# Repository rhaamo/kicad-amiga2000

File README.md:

# Amiga 2000 KiCAD Schematics and PCB

# Revision

Current schematics are based on 6.0 plus known 6.2 fixes.

Deviations from the original 6.2:
- The snapped resistor net around the 68k have been removed from schematics.
- The two res net soldered to U603 and U604 have a dedicated footprint on PCB
- The bridge C1/R1 also has footprint, same for R2 from U800
- The PST reset have dedicated footprint, diode have been removed
- There is an aditionnal header, J3, with OVR and INT2 breakout for accelerator cards, easier than clipping on chips
- Jumpers should have a default working configuration labelled on the PCB plus various notes
- The keyboard connector footprint have been modified to handle either the original one, or a standard MIDI one
- The battery terminals are just a two pins header, just plug some wires and use any battery you want aside or glued or whatever

# TODO

- Check if there is no useless local labels that could have generated spurious nets connected in the PCB

# Notes

The capacitors on the left of the POWER Connector are somewhat troubling if you don't have a lot of experience.

So the five caps should be placed like this (IGNORE the + footprint on the PCB):

- C400, GND pin on left
- C406, GND pin on left
- C408, GND pin on right
- C410, GND pin on left
- C412, GND pin on right

If using an A500-Flash from Retro 7-bit, U540 and U203 can't be socketted or they will be too high.

# Building

The file `amiga2000.csv` contains a full Mouser BOM, around ~150€.

Memory and RTC chip should be got from eBay, same for the PST reset thingy (U1).

The ISA (8bit and 16bit connectors) fits perfectly a full-length connector got from like an old PC motherboard.

The the table at the bottom of this README for a list of DigiKey and Mouser P/N for ZORRO, CoPro, Video and ISA slots.

Other chips (paula, denise, CIA, etc.) are got from a donor motherboard.

If building it for real: first test the PCB for short between GND and the various power lines (+5V, -5V, +12V, +5V_USER, etc.), the zorro should have all.

Then solder all the electrolytics caps, connect power, re-test all the lines.

Solder everything else, don't populate ICs yet, re-power and re-test.

Then you can add ICs and run DiagROM and then enjoy.

DO NOT POPULATE: J1, J2, C902, C917, R901, FB904, FB906, RP904, RP906, RP905, C230, C240, they are unpopulated on factory 6.2 rev, so, let them as-is.

# Testing

My first prototype have been tested with DiagROM v1.1.

Working: mouse, zorro listing of detected cards, composite video out, video out, serial (out at least), one audio ch (the other one should work too), keyboard.
Booting a workbench from the accelerator CF sorta work until noise issue or something make any disk I/O hang and crash.

Left to test: floppy, parallel port, if the RTC works properly.

The DiagROM detects 1024kB of chipmem, the extended test goes all the way up to 1023kB and then throw an error, I'm not sure if it's a DiagROM issue or just expected.

# Libraries

Uses libraries from https://dev.sigpipe.me/dashieelectronics/kicad_libraries

# Various tools

## extract_labels.py
NOTE: Broken since format change with KiCAD 7.0

Use this script to quickly extract all Global Labels from wanted sheets.

```
./extract_labels.py agnus.kicad_sch amiga2000.kicad_sch chipram.kicad_sch coprocessor\ slot.kicad_sch denise.kicad_sch expansion\ logic.kicad_sch parallel.kicad_sch paula.kicad_sch pc\ slots.kicad_sch power.kicad_sch processor.kicad_sch serial.kicad_sch zorro.kicad_sch
```

# License

CC0

# Sources

My own dying 6.2 A2000 board.

This pre-6.2 schematics, best scan quality available...:
- http://amiga.serveftp.net/Schematics/A2000_schematics/A2000_rev6_schematics_scanned.pdf

A big thanks for Floppie209 for his 1:1 board replica:
- https://github.com/Floppie209/Amiga2000-remake/

Whithout Floppie work I wouldn't have had enough motivation to sacrifice a sorta working board for measurements.

Documented 6.2 fixes: https://wiki.sigpipe.me/amiga:a2000:rev6.2fixes

# Random parts numbers

| for | Digikey PN | Mouser PN | Manufacturer PN | EOL |
|-----|------------|-----------|-----------------|-----|
| Zorro (100pins) | A121376-ND | 571-5645235-3 | 5645235-3 | no |
| CoPro (86pins) | A144213-ND | 571-1-5530843-0 | 1-5530843-0 | no |
| Video Slots and ISA16bit (36p) | A31716-ND |  571-5530843-3 | 5530843-3 | no |
| ISA 8bit (62) | A121053-ND |  571-7-5530843-0  | 7-5530843-0 | no |
| Full lenght ISA slots | A101941-ND |  571-5176139-2  | 5176139-2 | no |
| Power connector, 14 pins |   | 538-26-60-4140 | 26-60-4140 | no |

# Pictures

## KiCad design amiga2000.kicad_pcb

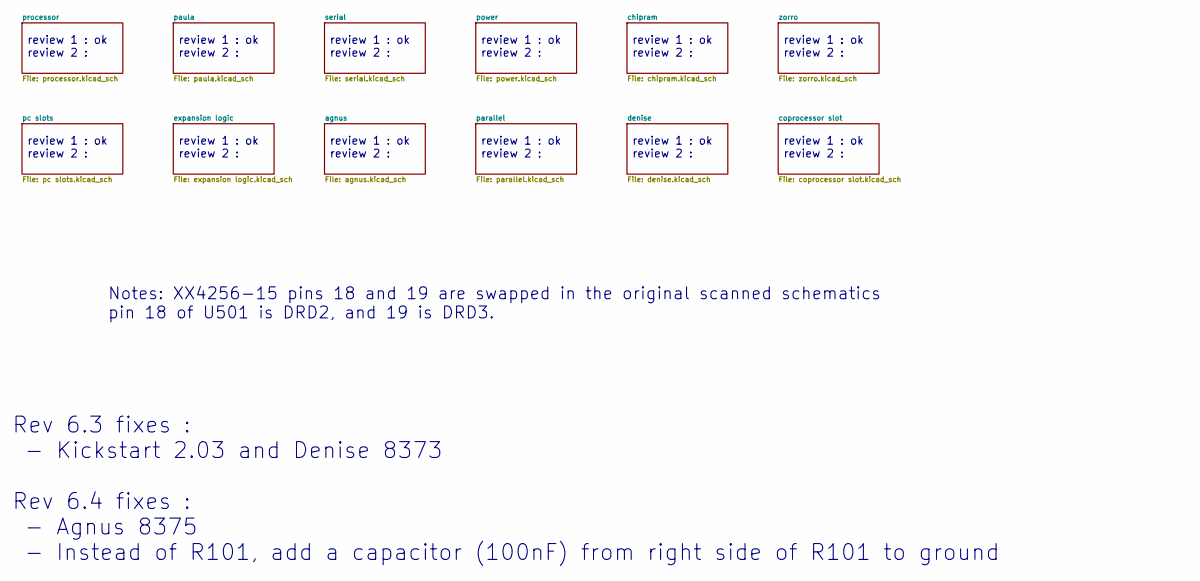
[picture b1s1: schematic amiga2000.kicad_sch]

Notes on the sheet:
review 1 : ok review 2 :
Notes: XX4256-15 pins 18 and 19 are swapped in the original scanned schematics pin 18 of U501 is DRD2, and 19 is DRD3.
Rev 6.3 fixes : - Kickstart 2.03 and Denise 8373 Rev 6.4 fixes : - Agnus 8375 - Instead of R101, add a capacitor (100nF) from right side of R101 to ground

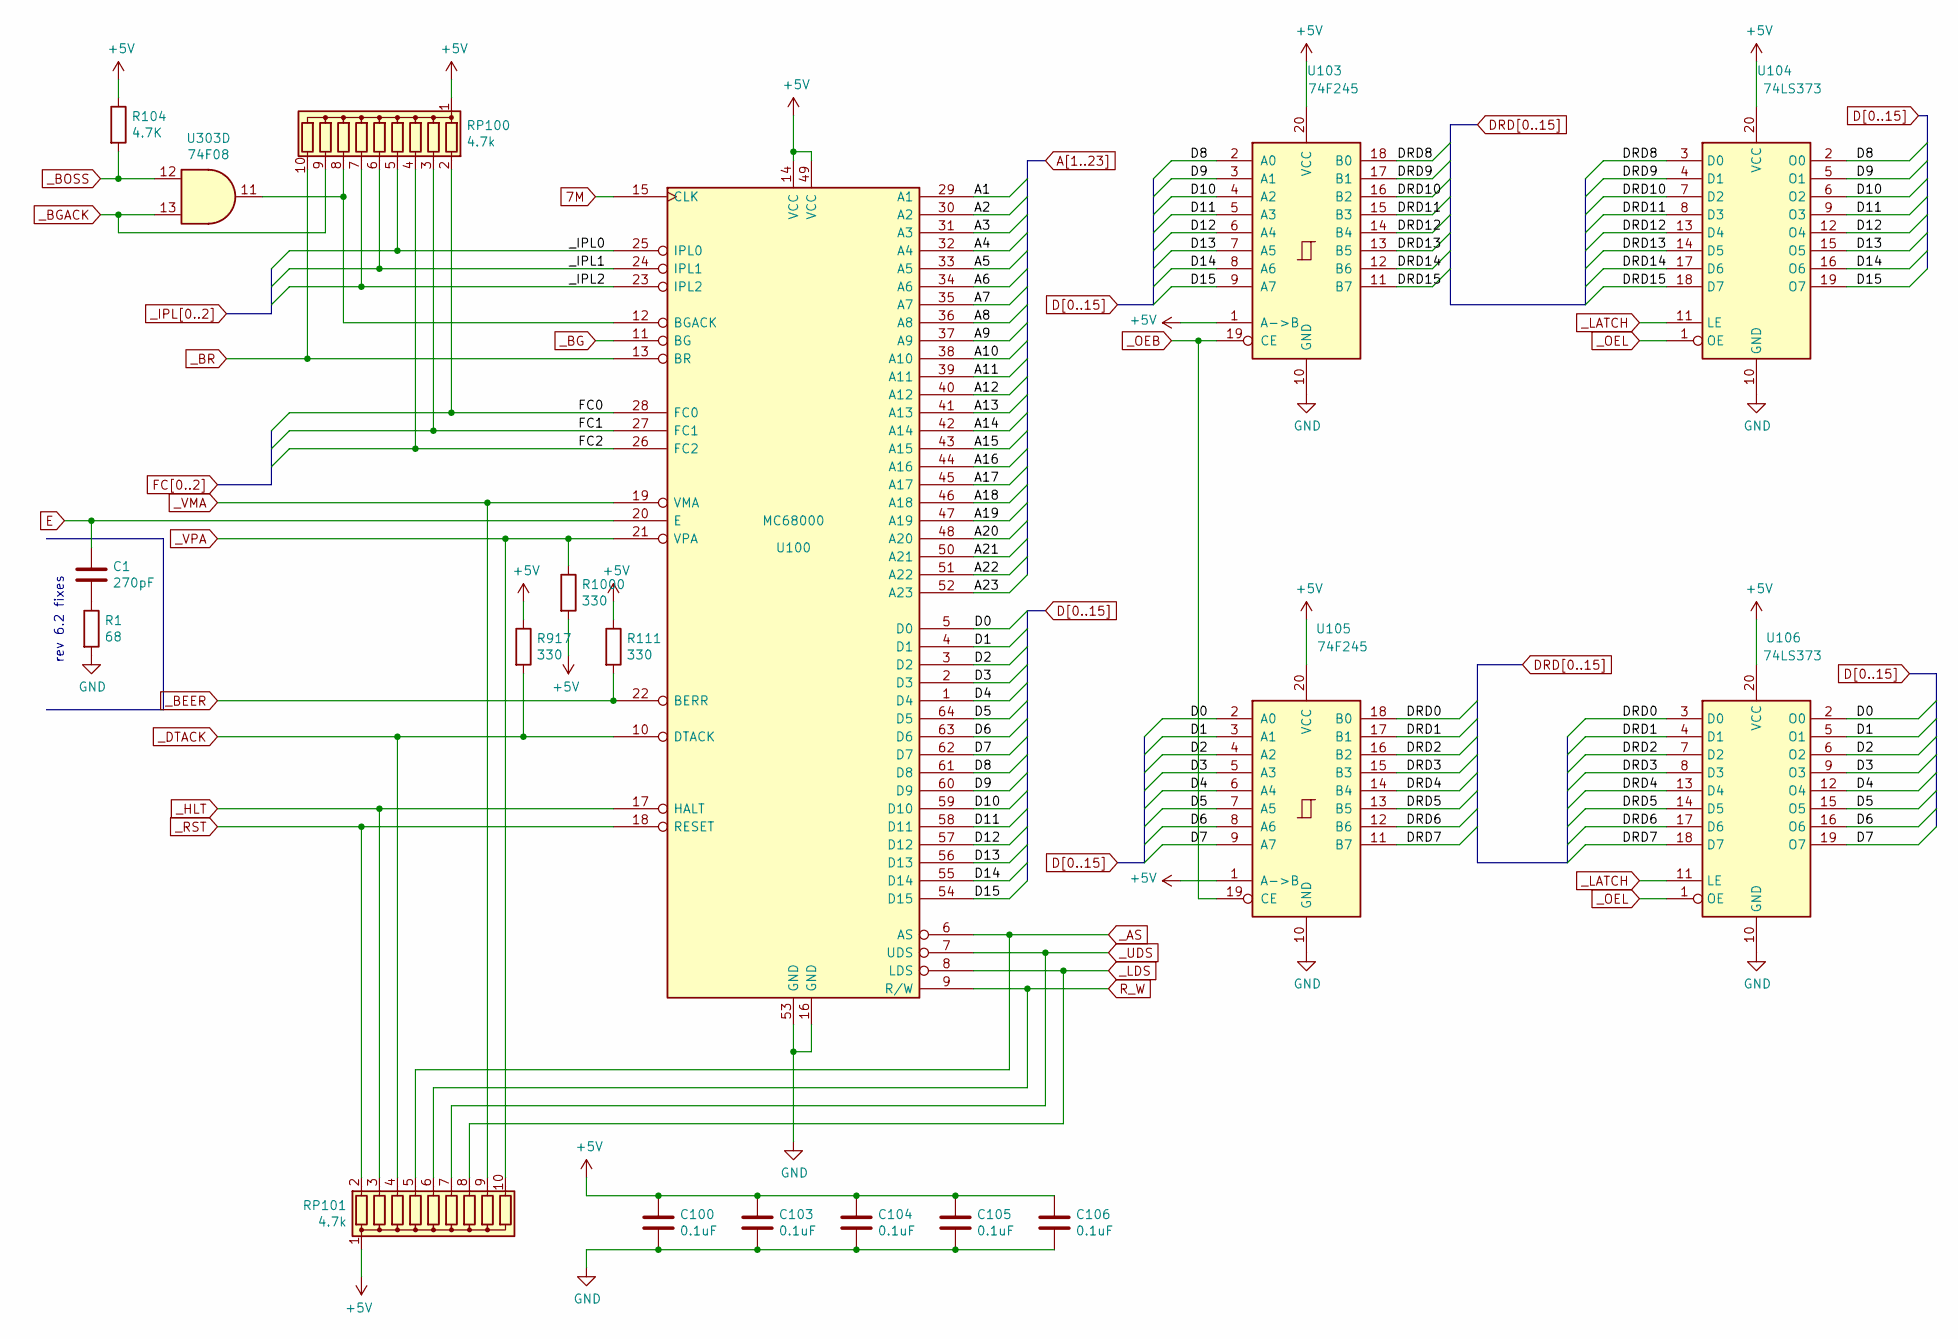
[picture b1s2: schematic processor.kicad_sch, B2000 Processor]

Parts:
C1: 270pF; C_Rect_L11.5mm_W2.6mm_P10.00mm_MKT
C100, C103, C104, C105, C106: 0.1uF; C_Rect_L11.5mm_W2.6mm_P10.00mm_MKT
R1: 68; R_Axial_DIN0207_L6.3mm_D2.5mm_P10.16mm_Horizontal
R104: 4.7K; R_Axial_DIN0207_L6.3mm_D2.5mm_P10.16mm_Horizontal
R111, R917, R1000: 330; R_Axial_DIN0207_L6.3mm_D2.5mm_P10.16mm_Horizontal
RP100, RP101: 4.7k; R_Array_SIP10
U100: MC68000; DIP-64_W22.86mm_Socket
U103, U105: 74F245; DIP-20_W7.62mm_Socket
U104, U106: 74LS373; DIP-20_W7.62mm_Socket
U303: 74F08; DIP-14_W7.62mm_Socket

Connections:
7M: U100.15 (CLK); also elsewhere on the board
A1: U100.29 (A1); also elsewhere on the board
A2: U100.30 (A2); also elsewhere on the board
A3: U100.31 (A3); also elsewhere on the board
A4: U100.32 (A4); also elsewhere on the board
A5: U100.33 (A5); also elsewhere on the board
A6: U100.34 (A6); also elsewhere on the board
A7: U100.35 (A7); also elsewhere on the board
A8: U100.36 (A8); also elsewhere on the board
A9: U100.37 (A9); also elsewhere on the board
A10: U100.38 (A10); also elsewhere on the board
A11: U100.39 (A11); also elsewhere on the board
A12: U100.40 (A12); also elsewhere on the board
A13: U100.41 (A13); also elsewhere on the board
A14: U100.42 (A14); also elsewhere on the board
A15: U100.43 (A15); also elsewhere on the board
A16: U100.44 (A16); also elsewhere on the board
A17: U100.45 (A17); also elsewhere on the board
A18: U100.46 (A18); also elsewhere on the board
A19: U100.47 (A19); also elsewhere on the board
A20: U100.48 (A20); also elsewhere on the board
A21: U100.50 (A21); also elsewhere on the board
A22: U100.51 (A22); also elsewhere on the board
A23: U100.52 (A23); also elsewhere on the board
D0: U100.5 (D0), U105.2 (A0), U106.2 (O0); also elsewhere on the board
D1: U100.4 (D1), U105.3 (A1), U106.5 (O1); also elsewhere on the board
D2: U100.3 (D2), U105.4 (A2), U106.6 (O2); also elsewhere on the board
D3: U100.2 (D3), U105.5 (A3), U106.9 (O3); also elsewhere on the board
D4: U100.1 (D4), U105.6 (A4), U106.12 (O4); also elsewhere on the board
D5: U100.64 (D5), U105.7 (A5), U106.15 (O5); also elsewhere on the board
D6: U100.63 (D6), U105.8 (A6), U106.16 (O6); also elsewhere on the board
D7: U100.62 (D7), U105.9 (A7), U106.19 (O7); also elsewhere on the board
D8: U100.61 (D8), U103.2 (A0), U104.2 (O0); also elsewhere on the board
D9: U100.60 (D9), U103.3 (A1), U104.5 (O1); also elsewhere on the board
D10: U100.59 (D10), U103.4 (A2), U104.6 (O2); also elsewhere on the board
D11: U100.58 (D11), U103.5 (A3), U104.9 (O3); also elsewhere on the board
D12: U100.57 (D12), U103.6 (A4), U104.12 (O4); also elsewhere on the board
D13: U100.56 (D13), U103.7 (A5), U104.15 (O5); also elsewhere on the board
D14: U100.55 (D14), U103.8 (A6), U104.16 (O6); also elsewhere on the board
D15: U100.54 (D15), U103.9 (A7), U104.19 (O7); also elsewhere on the board
DRD0: U105.18 (B0), U106.3 (D0); also elsewhere on the board
DRD1: U105.17 (B1), U106.4 (D1); also elsewhere on the board
DRD2: U105.16 (B2), U106.7 (D2); also elsewhere on the board
DRD3: U105.15 (B3), U106.8 (D3); also elsewhere on the board
DRD4: U105.14 (B4), U106.13 (D4); also elsewhere on the board
DRD5: U105.13 (B5), U106.14 (D5); also elsewhere on the board
DRD6: U105.12 (B6), U106.17 (D6); also elsewhere on the board
DRD7: U105.11 (B7), U106.18 (D7); also elsewhere on the board
DRD8: U103.18 (B0), U104.3 (D0); also elsewhere on the board
DRD9: U103.17 (B1), U104.4 (D1); also elsewhere on the board
DRD10: U103.16 (B2), U104.7 (D2); also elsewhere on the board
DRD11: U103.15 (B3), U104.8 (D3); also elsewhere on the board
DRD12: U103.14 (B4), U104.13 (D4); also elsewhere on the board
DRD13: U103.13 (B5), U104.14 (D5); also elsewhere on the board
DRD14: U103.12 (B6), U104.17 (D6); also elsewhere on the board
DRD15: U103.11 (B7), U104.18 (D7); also elsewhere on the board
E: C1.1, U100.20 (E); also elsewhere on the board
FC0: RP100.2 (R1), U100.28 (FC0); also elsewhere on the board
FC1: RP100.3 (R2), U100.27 (FC1); also elsewhere on the board
FC2: RP100.4 (R3), U100.26 (FC2); also elsewhere on the board
GND: C100.2, C103.2, C104.2, C105.2, C106.2, R1.2, U100.16 (GND), U100.53 (GND), U103.10 (GND), U104.10 (GND), U105.10 (GND), U106.10 (GND); also elsewhere on the board
unnamed: C1.2, R1.1
unnamed: RP100.8 (R7), U100.12 (BGACK), U303.11
R_W: RP101.6 (R5), U100.9 (R/W); also elsewhere on the board
_AS: RP101.5 (R4), U100.6 (AS); also elsewhere on the board
_BEER: R111.2, U100.22 (BERR); also elsewhere on the board
_BG: U100.11 (BG); also elsewhere on the board
_BGACK: RP100.9 (R8), U303.13; also elsewhere on the board
_BOSS: R104.2, U303.12; also elsewhere on the board
_BR: RP100.10 (R9), U100.13 (BR); also elsewhere on the board
_DTACK: R917.2, RP101.4 (R3), U100.10 (DTACK); also elsewhere on the board
_HLT: RP101.3 (R2), U100.17 (HALT); also elsewhere on the board
_IPL0: RP100.5 (R4), U100.25 (IPL0); also elsewhere on the board
_IPL1: RP100.6 (R5), U100.24 (IPL1); also elsewhere on the board
_IPL2: RP100.7 (R6), U100.23 (IPL2); also elsewhere on the board
_LATCH: U104.11 (LE), U106.11 (LE); also elsewhere on the board
_LDS: RP101.8 (R7), U100.8 (LDS); also elsewhere on the board
_OEB: U103.19 (CE), U105.19 (CE); also elsewhere on the board
_OEL: U104.1 (OE), U106.1 (OE); also elsewhere on the board
_RST: RP101.2 (R1), U100.18 (RESET); also elsewhere on the board
_UDS: RP101.7 (R6), U100.7 (UDS); also elsewhere on the board
_VMA: RP101.9 (R8), U100.19 (VMA); also elsewhere on the board
_VPA: R1000.1, RP101.10 (R9), U100.21 (VPA); also elsewhere on the board

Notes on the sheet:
rev 6.2 fixes

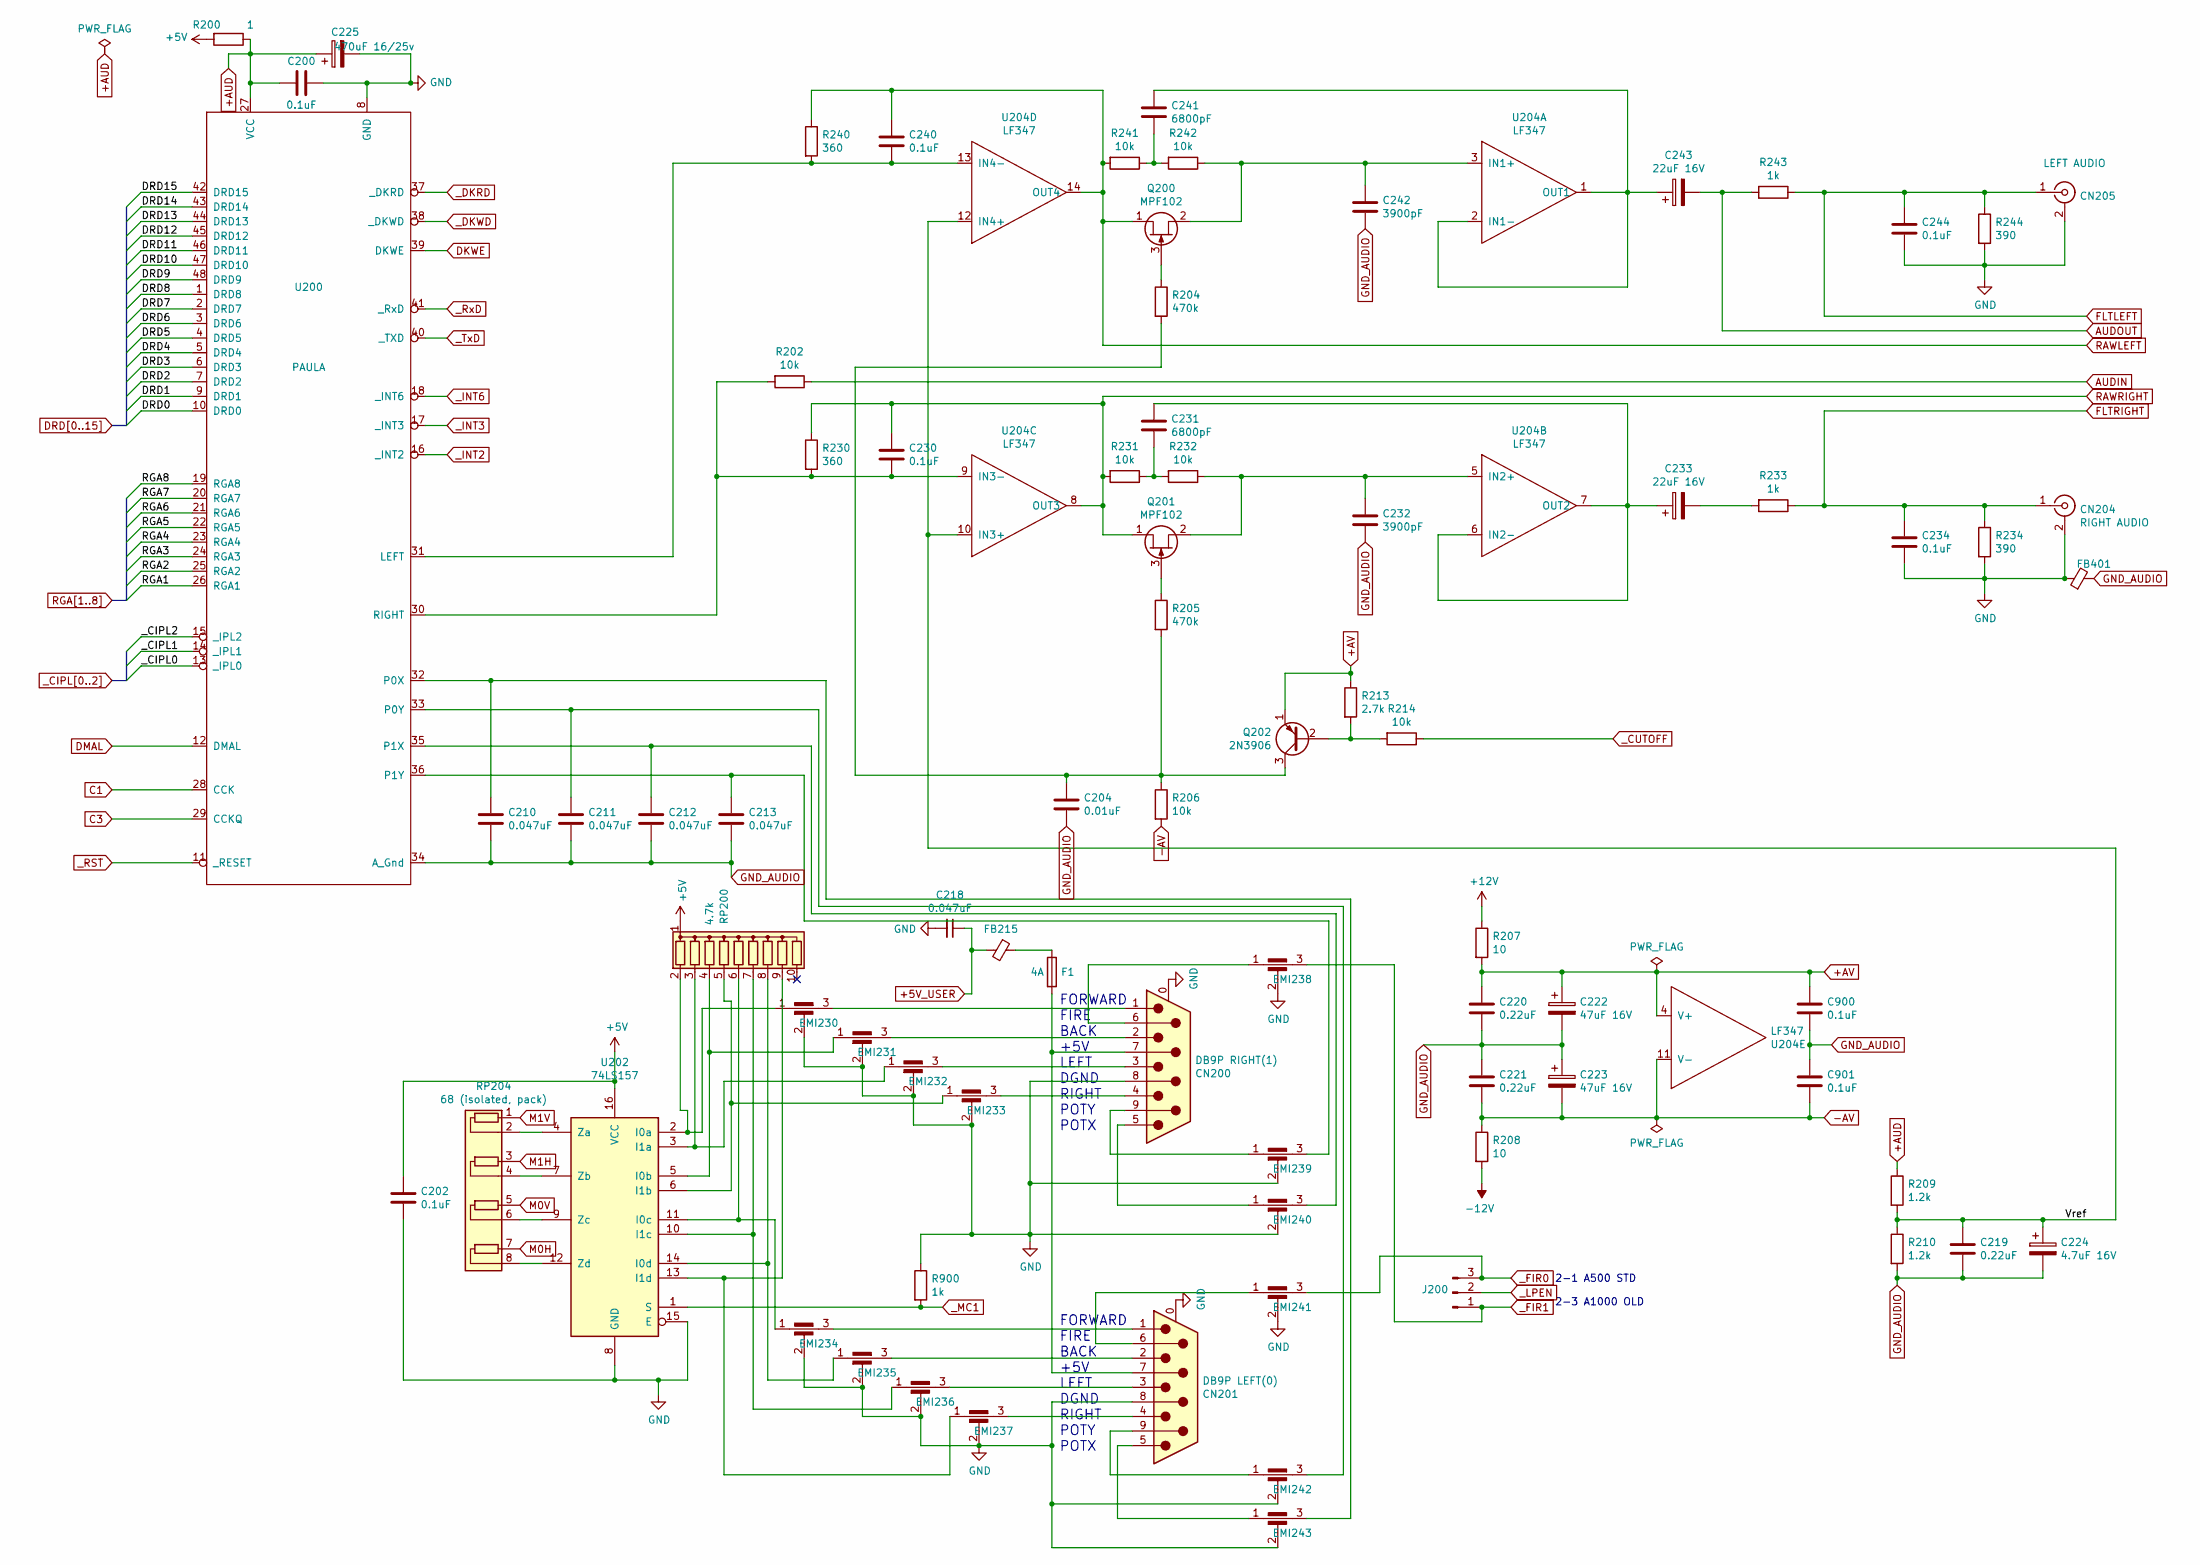
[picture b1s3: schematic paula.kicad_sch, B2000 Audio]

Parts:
C200, C202, C230, C234, C240, C244, C900, C901: 0.1uF; C_Rect_L11.5mm_W2.6mm_P10.00mm_MKT
C204: 0.01uF; C_Rect_L11.5mm_W2.6mm_P10.00mm_MKT
C210, C211, C212, C213, C218: 0.047uF; C_Rect_L11.5mm_W2.6mm_P10.00mm_MKT
C219, C220, C221: 0.22uF; C_Rect_L11.5mm_W2.6mm_P10.00mm_MKT
C222, C223: 47uF 16V; CP_Radial_Tantal_D5.5mm_P5.00mm
C224: 4.7uF 16V; CP_Radial_D5.0mm_P2.50mm
C225: 470uF 16/25v; CP_Radial_D10.0mm_P5.00mm
C231, C241: 6800pF; C_Rect_L11.5mm_W2.6mm_P10.00mm_MKT
C232, C242: 3900pF; C_Rect_L11.5mm_W2.6mm_P10.00mm_MKT
C233, C243: 22uF 16V; CP_Radial_Tantal_D5.0mm_P5.00mm
CN200: DB9P RIGHT(1); DSUB-9_Male_Horizontal_P2.77x2.84mm_EdgePinOffset7.70mm_Hou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
CN201: DB9P LEFT(0); DSUB-9_Male_Horizontal_P2.77x2.84mm_EdgePinOffset7.70mm_Hou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
CN204: RIGHT AUDIO; RCA
CN205: LEFT AUDIO; RCA
EMI230, EMI231, EMI232, EMI233, EMI234, EMI235, EMI236, EMI237, EMI238, EMI239, EMI240, EMI241, EMI242, EMI243: 6.8nF (Type F 682); EMI_FILTER
F1: 4A; C_Rect_L11.5mm_W2.0mm_P10.00mm_MKT
FB215, FB401: Ferrite_Bead_Small; L_Axial_L7.0mm_D3.3mm_P10.16mm_Horizontal_Fastron_MICC
J200: Conn_01x03_Male; PinHeader_1x03_P2.54mm_Vertical
Q200, Q201: MPF102; TO-92_Inline
Q202: 2N3906; TO-92_Inline
R200: 1; R_Axial_DIN0207_L6.3mm_D2.5mm_P10.16mm_Horizontal
R202, R206, R214, R231, R232, R241, R242: 10k; R_Axial_DIN0207_L6.3mm_D2.5mm_P10.16mm_Horizontal
R204, R205: 470k; R_Axial_DIN0207_L6.3mm_D2.5mm_P10.16mm_Horizontal
R207, R208: 10; R_Axial_DIN0207_L6.3mm_D2.5mm_P10.16mm_Horizontal
R209, R210: 1.2k; R_Axial_DIN0207_L6.3mm_D2.5mm_P10.16mm_Horizontal
R213: 2.7k; R_Axial_DIN0207_L6.3mm_D2.5mm_P10.16mm_Horizontal
R230, R240: 360; R_Axial_DIN0207_L6.3mm_D2.5mm_P10.16mm_Horizontal
R233, R243, R900: 1k; R_Axial_DIN0207_L6.3mm_D2.5mm_P10.16mm_Horizontal
R234, R244: 390; R_Axial_DIN0207_L6.3mm_D2.5mm_P10.16mm_Horizontal
RP200: 4.7k; R_Array_SIP10
RP204: 68 (isolated, pack); R_Array_SIP8
U200: PAULA; DIP-48_W15.24mm_Socket
U202: 74LS157; DIP-16_W7.62mm_Socket
U204: LF347; DIP-14_W7.62mm_Socket

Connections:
+5V_USER: C218.1, FB215.2; also elsewhere on the board
+12V: R207.1; also elsewhere on the board
+AUD: C200.2, C225.1, R200.1, R209.1, U200.27 (VCC)
+AV: C220.1, C222.1, C900.1, Q202.1 (E), R207.2, R213.1, U204.4 (V+)
-12V: R208.2; also elsewhere on the board
-AV: C221.2, C223.2, C901.2, R206.2, R208.1, U204.11 (V-)
/paula/Vref: C219.1, C224.1, R209.2, R210.1, U204.10 (IN3+), U204.12 (IN4+)
AUDIN: R202.1; also elsewhere on the board
AUDOUT: C243.2, R243.2; also elsewhere on the board
C1: U200.28 (CCK); also elsewhere on the board
C3: U200.29 (CCKQ); also elsewhere on the board
DKWE: U200.39 (DKWE); also elsewhere on the board
DMAL: U200.12 (DMAL); also elsewhere on the board
DRD0: U200.10 (DRD0); also elsewhere on the board
DRD1: U200.9 (DRD1); also elsewhere on the board
DRD2: U200.7 (DRD2); also elsewhere on the board
DRD3: U200.6 (DRD3); also elsewhere on the board
DRD4: U200.5 (DRD4); also elsewhere on the board
DRD5: U200.4 (DRD5); also elsewhere on the board
DRD6: U200.3 (DRD6); also elsewhere on the board
DRD7: U200.2 (DRD7); also elsewhere on the board
DRD8: U200.1 (DRD8); also elsewhere on the board
DRD9: U200.48 (DRD9); also elsewhere on the board
DRD10: U200.47 (DRD10); also elsewhere on the board
DRD11: U200.46 (DRD11); also elsewhere on the board
DRD12: U200.45 (DRD12); also elsewhere on the board
DRD13: U200.44 (DRD13); also elsewhere on the board
DRD14: U200.43 (DRD14); also elsewhere on the board
DRD15: U200.42 (DRD15); also elsewhere on the board
FLTLEFT: C244.1, CN205.1 (In), R243.1, R244.1; also elsewhere on the board
FLTRIGHT: C234.1, CN204.1 (In), R233.1, R234.1; also elsewhere on the board
GND: C200.1, C202.2, C218.2, C225.2, C234.2, C244.2, CN200.0 (PAD), CN200.8, CN201.0 (PAD), CN201.8, CN204.2 (Ext), CN205.2 (Ext), EMI230.2, EMI231.2, EMI232.2, EMI233.2, EMI234.2, EMI235.2, EMI236.2, EMI237.2, EMI238.2, EMI239.2, EMI240.2, EMI241.2, EMI242.2, EMI243.2, FB401.1, R234.2, R244.2, R900.1, U200.8 (GND), U202.8 (GND), U202.15 (E); also elsewhere on the board
GND_AUDIO: C204.2, C210.2, C211.2, C212.2, C213.2, C219.2, C220.2, C221.1, C222.2, C223.1, C224.2, C232.2, C242.2, C900.2, C901.1, FB401.2, R210.2, U200.34 (A_Gnd); also elsewhere on the board
M0H: RP204.7 (R4.1); also elsewhere on the board
M0V: RP204.5 (R3.1); also elsewhere on the board
M1H: RP204.3 (R2.1); also elsewhere on the board
M1V: RP204.1 (R1.1); also elsewhere on the board
unnamed: C204.1, Q202.3 (C), R204.2, R205.2, R206.1
unnamed: C210.1, EMI243.3, U200.32 (P0X)
unnamed: C211.1, EMI242.3, U200.33 (P0Y)
unnamed: C212.1, EMI240.3, U200.35 (P1X)
unnamed: C213.1, EMI239.3, U200.36 (P1Y)
unnamed: C230.2, R202.2, R230.2, U200.30 (RIGHT), U204.9 (IN3-)
unnamed: C231.1, C233.1, U204.6 (IN2-), U204.7 (OUT2)
unnamed: C231.2, R231.1, R232.2
unnamed: C232.1, Q201.2 (S), R232.1, U204.5 (IN2+)
unnamed: C233.2, R233.2
unnamed: C240.2, R240.2, U200.31 (LEFT), U204.13 (IN4-)
unnamed: C241.1, C243.1, U204.1 (OUT1), U204.2 (IN1-)
unnamed: C241.2, R241.1, R242.2
unnamed: C242.1, Q200.2 (S), R242.1, U204.3 (IN1+)
unnamed: EMI230.1, RP200.2 (R1), U202.2 (I0a)
unnamed: EMI231.1, RP200.4 (R3), U202.5 (I0b)
unnamed: EMI232.1, RP200.3 (R2), U202.3 (I1a)
unnamed: EMI233.1, RP200.5 (R4), U202.6 (I1b)
unnamed: EMI234.1, RP200.6 (R5), U202.11 (I0c)
unnamed: EMI235.1, RP200.8 (R7), U202.14 (I0d)
unnamed: EMI236.1, RP200.7 (R6), U202.10 (I1c)
unnamed: EMI237.1, RP200.9 (R8), U202.13 (I1d)
unnamed: F1.1, FB215.1
unnamed: Q200.3 (G), R204.1
unnamed: Q201.3 (G), R205.1
unnamed: Q202.2 (B), R213.2, R214.2
unnamed: RP204.2 (R1.2), U202.4 (Za)
unnamed: RP204.4 (R2.2), U202.7 (Zb)
unnamed: RP204.6 (R3.2), U202.9 (Zc)
unnamed: RP204.8 (R4.2), U202.12 (Zd)
RAWLEFT: C240.1, Q200.1 (D), R240.1, R241.2, U204.14 (OUT4); also elsewhere on the board
RAWRIGHT: C230.1, Q201.1 (D), R230.1, R231.2, U204.8 (OUT3); also elsewhere on the board
RGA1: U200.26 (RGA1); also elsewhere on the board
RGA2: U200.25 (RGA2); also elsewhere on the board
RGA3: U200.24 (RGA3); also elsewhere on the board
RGA4: U200.23 (RGA4); also elsewhere on the board
RGA5: U200.22 (RGA5); also elsewhere on the board
RGA6: U200.21 (RGA6); also elsewhere on the board
RGA7: U200.20 (RGA7); also elsewhere on the board
RGA8: U200.19 (RGA8); also elsewhere on the board
_CIPL0: U200.13 (_IPL0); also elsewhere on the board
_CIPL1: U200.14 (_IPL1); also elsewhere on the board
_CIPL2: U200.15 (_IPL2); also elsewhere on the board
_CUTOFF: R214.1; also elsewhere on the board
_DKWD: U200.38 (_DKWD); also elsewhere on the board
_FIR0: EMI241.3, J200.3; also elsewhere on the board
_FIR1: EMI238.3, J200.1; also elsewhere on the board
_INT2: U200.16 (_INT2); also elsewhere on the board
_INT3: U200.17 (_INT3); also elsewhere on the board
_INT6: U200.18 (_INT6); also elsewhere on the board
_LPEN: J200.2; also elsewhere on the board
_MC1: R900.2, U202.1 (S); also elsewhere on the board
_RST: U200.11 (_RESET); also elsewhere on the board
_RxD: U200.41 (_RxD); also elsewhere on the board
_TxD: U200.40 (_TXD); also elsewhere on the board

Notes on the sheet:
FORWARD FIRE BACK +5V LEFT DGND RIGHT POTY POTX
2-1 A500 STD 2-3 A1000 OLD

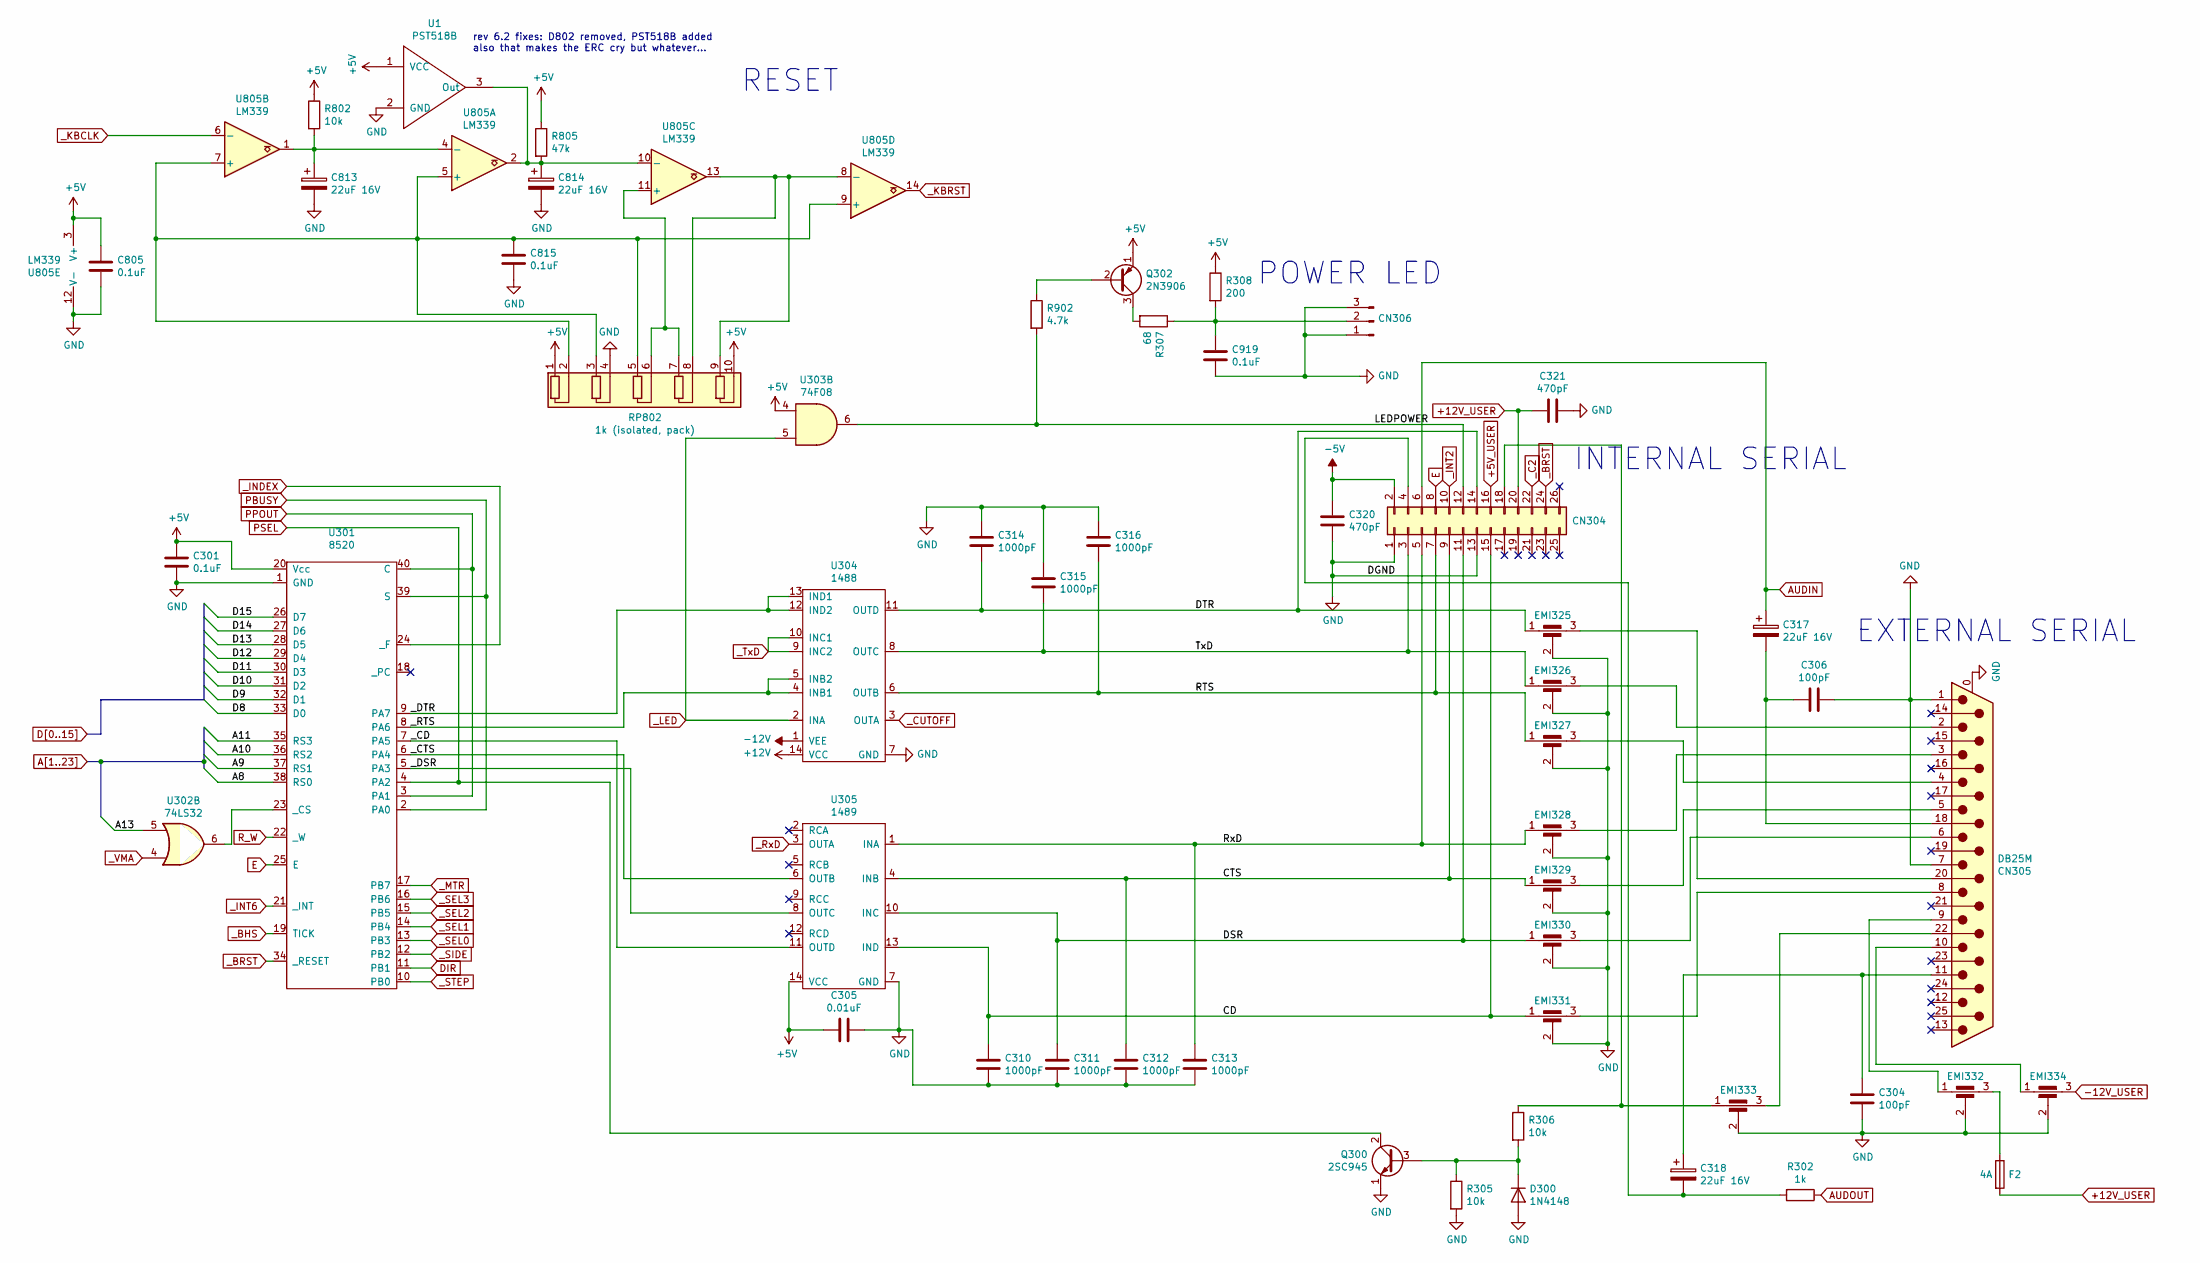
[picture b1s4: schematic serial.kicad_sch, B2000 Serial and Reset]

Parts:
C301, C805, C815, C919: 0.1uF; C_Rect_L11.5mm_W2.6mm_P10.00mm_MKT
C304, C306: 100pF; C_Rect_L11.5mm_W2.6mm_P10.00mm_MKT
C305: 0.01uF; C_Rect_L11.5mm_W2.6mm_P10.00mm_MKT
C310, C311, C312, C313, C314, C315, C316: 1000pF; C_Rect_L7.0mm_W2.0mm_P5.00mm
C317, C318, C813, C814: 22uF 16V; CP_Radial_Tantal_D5.0mm_P5.00mm
C320, C321: 470pF; C_Rect_L7.0mm_W2.0mm_P5.00mm
CN304: Conn_02x13_Odd_Even; PinHeader_2x13_P2.54mm_Vertical
CN305: DB25M; DSUB-25_Male_Horizontal_P2.77x2.84mm_EdgePinOffset7.70mm_Ho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
CN306: Conn_01x03_Male; PinHeader_1x03_P2.54mm_Vertical
D300: 1N4148; D_DO-35_SOD27_P7.62mm_Horizontal
EMI325, EMI326, EMI327, EMI328, EMI329, EMI330, EMI331, EMI332, EMI333, EMI334: 330pF (Type F 331); EMI_FILTER
F2: 4A; C_Rect_L11.5mm_W2.0mm_P10.00mm_MKT
Q300: 2SC945; TO-92_Inline
Q302: 2N3906; TO-92_Inline
R302: 1k; R_Axial_DIN0207_L6.3mm_D2.5mm_P10.16mm_Horizontal
R305, R306, R802: 10k; R_Axial_DIN0207_L6.3mm_D2.5mm_P10.16mm_Horizontal
R307: 68; R_Axial_DIN0207_L6.3mm_D2.5mm_P10.16mm_Horizontal
R308: 200; R_Axial_DIN0207_L6.3mm_D2.5mm_P10.16mm_Horizontal
R805: 47k; R_Axial_DIN0207_L6.3mm_D2.5mm_P10.16mm_Horizontal
R902: 4.7k; R_Axial_DIN0207_L6.3mm_D2.5mm_P10.16mm_Horizontal
RP802: 1k (isolated, pack); R_Array_SIP10
U1: PST518B; TO-92L_Inline
U301: 8520; DIP-40_W15.24mm_Socket
U302: 74LS32; DIP-14_W7.62mm_Socket
U303: 74F08; DIP-14_W7.62mm_Socket
U304: 1488; DIP-14_W7.62mm_Socket
U305: 1489; DIP-14_W7.62mm_Socket
U805: LM339; DIP-14_W7.62mm_Socket

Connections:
+5V_USER: CN304.16; also elsewhere on the board
+12V: U304.14 (VCC); also elsewhere on the board
+12V_USER: C321.2, CN304.20, F2.2; also elsewhere on the board
-5V: C320.1, CN304.2; also elsewhere on the board
-12V: U304.1 (VEE); also elsewhere on the board
-12V_USER: EMI334.3; also elsewhere on the board
/serial/CD: C310.1, CN304.15, EMI331.1, U305.13 (IND)
/serial/CTS: C312.1, CN304.9, EMI329.1, U305.4 (INB)
/serial/DSR: C311.1, CN304.11, EMI330.1, U305.10 (INC)
/serial/DTR: C314.2, CN304.14, EMI325.1, U304.11 (OUTD)
/serial/LEDPOWER: CN304.12, R902.2, U303.6
/serial/RTS: C316.2, CN304.7, EMI327.1, U304.6 (OUTB)
/serial/RxD: C313.1, CN304.5, EMI328.1, U305.1 (INA)
/serial/TxD: C315.2, CN304.3, EMI326.1, U304.8 (OUTC)
/serial/_CD: U301.7 (PA5), U305.11 (OUTD)
/serial/_CTS: U301.6 (PA4), U305.6 (OUTB)
/serial/_DSR: U301.5 (PA3), U305.8 (OUTC)
/serial/_DTR: U301.9 (PA7), U304.12 (IND2), U304.13 (IND1)
/serial/_RTS: U301.8 (PA6), U304.4 (INB1), U304.5 (INB2)
A8: U301.38 (RS0); also elsewhere on the board
A9: U301.37 (RS1); also elsewhere on the board
A10: U301.36 (RS2); also elsewhere on the board
A11: U301.35 (RS3); also elsewhere on the board
A13: U302.5; also elsewhere on the board
AUDIN: C317.1, CN304.6; also elsewhere on the board
AUDOUT: R302.1; also elsewhere on the board
D8: U301.33 (D0); also elsewhere on the board
D9: U301.32 (D1); also elsewhere on the board
D10: U301.31 (D2); also elsewhere on the board
D11: U301.30 (D3); also elsewhere on the board
D12: U301.29 (D4); also elsewhere on the board
D13: U301.28 (D5); also elsewhere on the board
D14: U301.27 (D6); also elsewhere on the board
D15: U301.26 (D7); also elsewhere on the board
DIR: U301.11 (PB1); also elsewhere on the board
E: CN304.8, U301.25 (E); also elsewhere on the board
GND: C301.2, C304.2, C305.1, C306.1, C310.2, C311.2, C312.2, C313.2, C314.1, C315.1, C316.1, C320.2, C321.1, C805.2, C813.2, C814.2, C815.2, C919.2, CN304.1, CN304.13, CN305.0 (PAD), CN305.1, CN305.7, CN306.1, CN306.3, D300.2 (A), EMI325.2, EMI326.2, EMI327.2, EMI328.2, EMI329.2, EMI330.2, EMI331.2, EMI332.2, EMI333.2, EMI334.2, Q300.1 (E), R305.2, RP802.4 (R2.2), U1.2 (GND), U301.1 (GND), U304.7 (GND), U305.7 (GND), U805.12 (V-); also elsewhere on the board
unnamed: C304.1, C318.1, CN305.11
unnamed: C306.2, C317.2, CN305.18
unnamed: C318.2, CN304.4, R302.2
unnamed: C813.1, R802.2, U805.1, U805.4 (-)
unnamed: C814.1, R805.2, U1.3 (Out), U805.2, U805.10 (-)
unnamed: C815.1, RP802.2 (R1.2), RP802.3 (R2.1), RP802.5 (R3.1), U805.5 (+), U805.7 (+), U805.9 (+)
unnamed: C919.1, CN306.2, R307.1, R308.2
unnamed: CN304.18, EMI333.1, R306.1
unnamed: CN305.2, EMI326.3
unnamed: CN305.3, EMI328.3
unnamed: CN305.4, EMI327.3
unnamed: CN305.5, EMI329.3
unnamed: CN305.6, EMI330.3
unnamed: CN305.8, EMI331.3
unnamed: CN305.9, EMI332.1
unnamed: CN305.10, EMI334.1
unnamed: CN305.20, EMI325.3
unnamed: CN305.22, EMI333.3
unnamed: D300.1 (K), Q300.3 (B), R305.1, R306.2
unnamed: EMI332.3, F2.1
unnamed: Q302.2 (B), R902.1
unnamed: Q302.3 (C), R307.2
unnamed: RP802.6 (R3.2), RP802.7 (R4.1), U805.11 (+)
unnamed: RP802.8 (R4.2), RP802.9 (R5.1), U805.8 (-), U805.13
unnamed: U301.23 (_CS), U302.6
PBUSY: U301.2 (PA0), U301.39 (S); also elsewhere on the board
PPOUT: U301.3 (PA1), U301.40 (C); also elsewhere on the board
PSEL: Q300.2 (C), U301.4 (PA2); also elsewhere on the board
R_W: U301.22 (_W); also elsewhere on the board
_BHS: U301.19 (TICK); also elsewhere on the board
_BRST: CN304.24, U301.34 (_RESET); also elsewhere on the board
_C2: CN304.22; also elsewhere on the board
_CUTOFF: U304.3 (OUTA); also elsewhere on the board
_INDEX: U301.24 (_F); also elsewhere on the board
_INT2: CN304.10; also elsewhere on the board
_INT6: U301.21 (_INT); also elsewhere on the board
_KBCLK: U805.6 (-); also elsewhere on the board
_KBRST: U805.14; also elsewhere on the board
_LED: U303.5, U304.2 (INA); also elsewhere on the board
_MTR: U301.17 (PB7); also elsewhere on the board
_RxD: U305.3 (OUTA); also elsewhere on the board
_SEL0: U301.13 (PB3); also elsewhere on the board
_SEL2: U301.15 (PB5); also elsewhere on the board
_SEL3: U301.16 (PB6); also elsewhere on the board
_SIDE: U301.12 (PB2); also elsewhere on the board
_STEP: U301.10 (PB0); also elsewhere on the board
_TxD: U304.9 (INC2), U304.10 (INC1); also elsewhere on the board
_VMA: U302.4; also elsewhere on the board

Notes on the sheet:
RESET
POWER LED
EXTERNAL SERIAL
INTERNAL SERIAL
rev 6.2 fixes: D802 removed, PST518B added also that makes the ERC cry but whatever...
